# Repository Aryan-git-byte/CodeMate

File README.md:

# CodeMate - My Dev Macropad
hiii! this is my hackpad submission. built a 3x3 macropad to speed up my coding workflow

## what it does
- 9 mechanical switches in a 3x3 grid for shortcuts and macros
- rotary encoder for volume control
- 0.91" OLED that shows which key i just pressed (flashes for 1.5sec then shows "ready")
- 6 RGB LEDs that breathe in warm amber and pulse when i hit keys
- runs on Arduino (not KMK anymore) so i can use TinyUSB

## PCB
heres what the electronics look like:

| Schematic | PCB |
|-----------|-----|
|  |  |

took me a few tries to get the routing right but it works now

[x] I ran DRC and there are 0 errors but few silkscreen warnings

## Case
made in fusion360. fits everything together with M3 screws and heatset inserts

along with the top:

the switches poke through the top plate and the oled sits in a cutout. pretty clean imo

## Firmware
rewrote it in Arduino because i wanted better HID support. NO LAYERS anymore, just 9 coding shortcuts that i actually use:

**The Layout:**
```
Comment      | Format Code    | Duplicate Line
Run (F5)     | Terminal       | Close Tab
git status   | git commit     | git push
```

Encoder: Volume up/down (stays the same always)

### what each key does
- **Key 0:** Toggle comment (Ctrl+/)
- **Key 1:** Format code (Shift+Alt+F)
- **Key 2:** Duplicate line (Shift+Alt+Down)
- **Key 3:** Run code (F5)
- **Key 4:** Toggle terminal (Ctrl+`)
- **Key 5:** Close tab (Ctrl+W)
- **Key 6:** Opens terminal + runs `git status`
- **Key 7:** Opens terminal + types `git commit -m ""` with cursor inside quotes
- **Key 8:** Opens terminal + runs `git push`

git commands automatically open the VS Code terminal first (Ctrl+Shift+`) then type the command. super handy

### LED behavior
- **Normal:** slow breathing effect (10% to 40% brightness) in warm amber
- **When you press a key:** the LED near that key flashes bright then fades back to breathing
- **Color:** warm amber (255, 140, 0) because one of my LEDs has a dead blue channel lol

the oled shows which key i pressed for 1.5 seconds then goes back to showing "ready"

[x] no api keys or passwords in the code

## BOM
what you need to build this:
- 1x XIAO RP2040
- 9x Cherry MX switches  
- 9x 1N4148 diodes
- 6x SK6812 MINI-E LEDs (NOT WS2812B, different color order)
- 1x 0.91" SSD1306 OLED (128x32, I2C)
- 1x EC11 rotary encoder
- 1x 330Ω resistor (for LED data line - optional but recommended)
- 1x 1000µF capacitor (bulk cap for LEDs - optional but recommended)
- 4x M3x16mm screws
- 4x M3x5mmx4mm heatset inserts

## notes
this was fun to make! spent way too much time tweaking the firmware but learned a lot about Arduino HID and how SK6812 LEDs work differently from WS2812B.

switched from KMK to Arduino because i wanted proper keyboard+consumer HID support and the encoder was being weird in KMK. plus now i can do the breathing LED effect which looks way cooler than static colors

GG

# this is the prototype:

## and when buttons are pressed it looks like:

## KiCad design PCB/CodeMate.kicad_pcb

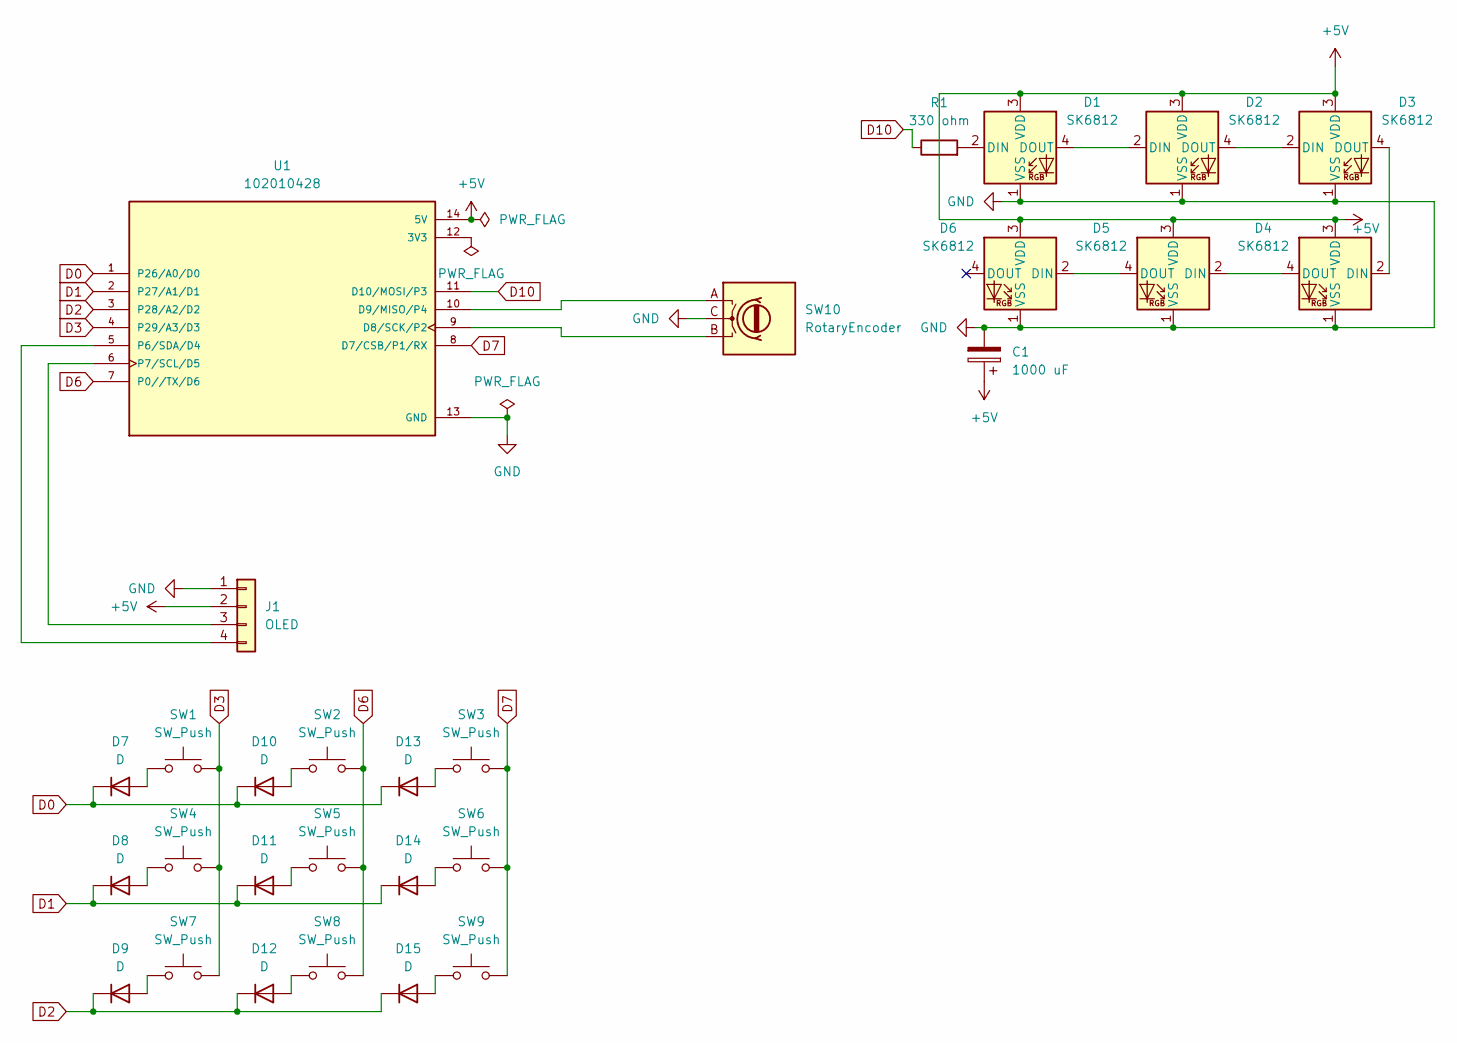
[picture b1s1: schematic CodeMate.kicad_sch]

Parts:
C1: 1000 uF; CP_Radial_D8.0mm_P3.50mm
D1, D2, D3, D4, D5, D6: SK6812; LED_SK6812MINI_PLCC4_3.5x3.5mm_P1.75mm
D7, D8, D9, D10, D11, D12, D13, D14, D15: D; D_DO-35_SOD27_P7.62mm_Horizontal
J1: OLED; PinHeader_1x04_P2.54mm_Vertical
R1: 330 ohm; R_Axial_DIN0207_L6.3mm_D2.5mm_P7.62mm_Horizontal
SW1, SW2, SW3, SW4, SW5, SW6, SW7, SW8, SW9: SW_Push; SW_Cherry_MX_1.00u_PCB
SW10: RotaryEncoder; RotaryEncoder_Alps_EC11E-Switch_Vertical_H20mm_CircularMoun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
U1: 102010428; XIAO-RP2040-DIP; PARTREV 1.3

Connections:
+5V: C1.1, D1.3 (VDD), D2.3 (VDD), D3.3 (VDD), D4.3 (VDD), D5.3 (VDD), D6.3 (VDD), J1.2, U1.14 (5V)
D0: D7.1 (K), D10.1 (K), D13.1 (K), U1.1 (P26/A0/D0)
D1: D8.1 (K), D11.1 (K), D14.1 (K), U1.2 (P27/A1/D1)
D2: D9.1 (K), D12.1 (K), D15.1 (K), U1.3 (P28/A2/D2)
D3: SW1.2, SW4.2, SW7.2, U1.4 (P29/A3/D3)
D6: SW2.2, SW5.2, SW8.2, U1.7 (P0//TX/D6)
D7: SW3.2, SW6.2, SW9.2, U1.8 (D7/CSB/P1/RX)
D10: R1.1, U1.11 (D10/MOSI/P3)
GND: C1.2, D1.1 (VSS), D2.1 (VSS), D3.1 (VSS), D4.1 (VSS), D5.1 (VSS), D6.1 (VSS), J1.1, SW10.C, U1.13 (GND)
unnamed: D1.2 (DIN), R1.2
unnamed: D1.4 (DOUT), D2.2 (DIN)
unnamed: D2.4 (DOUT), D3.2 (DIN)
unnamed: D3.4 (DOUT), D4.2 (DIN)
unnamed: D4.4 (DOUT), D5.2 (DIN)
unnamed: D5.4 (DOUT), D6.2 (DIN)
unnamed: D7.2 (A), SW1.1
unnamed: D8.2 (A), SW4.1
unnamed: D9.2 (A), SW7.1
unnamed: D10.2 (A), SW2.1
unnamed: D11.2 (A), SW5.1
unnamed: D12.2 (A), SW8.1
unnamed: D13.2 (A), SW3.1
unnamed: D14.2 (A), SW6.1
unnamed: D15.2 (A), SW9.1
unnamed: J1.3, U1.6 (P7/SCL/D5)
unnamed: J1.4, U1.5 (P6/SDA/D4)
unnamed: SW10.B, U1.9 (D8/SCK/P2)
unnamed: SW10.A, U1.10 (D9/MISO/P4)

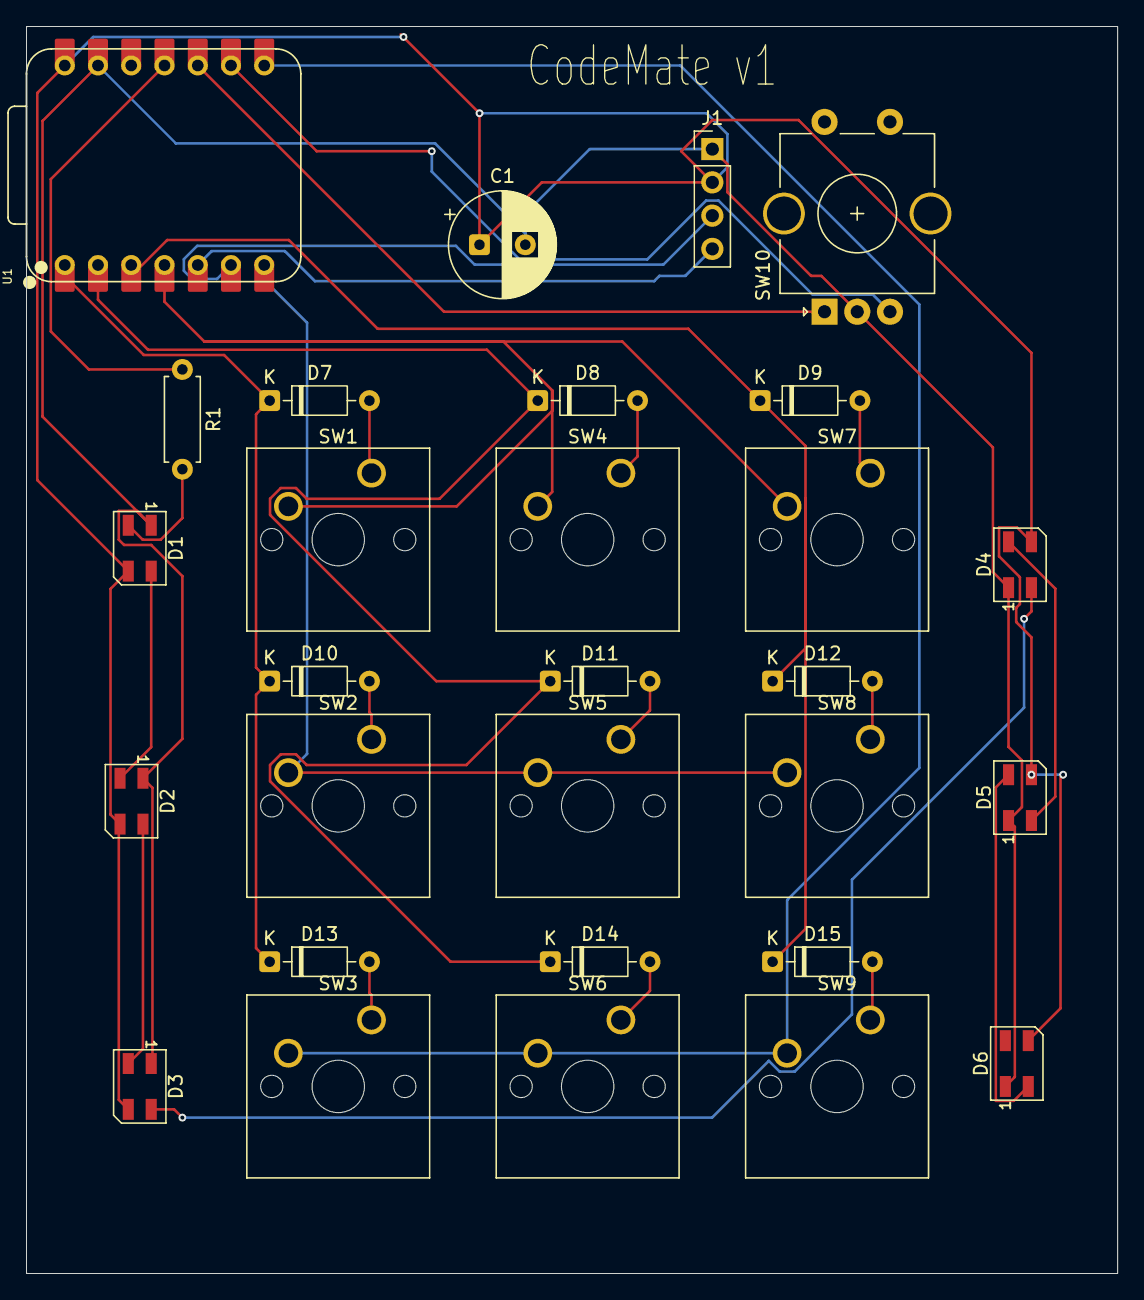
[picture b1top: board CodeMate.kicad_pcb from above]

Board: 2 copper layers, 83.3 x 95.2 mm, 29 parts (0 on the bottom side), 28 nets.

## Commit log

2026-01-25 addedd documentations
2026-01-25 updated documentations
2026-01-25 Rename CAD-body.png to cad-body.png
2026-01-29 Update README to include TODO for resource link
    Add a note to include a resource download hyperlink.
2026-01-29 Add test line Co-authored-by: FriendName <friend@email.com>
2026-01-29 Add a note of appreciation to README
2026-01-29 Create LICENSE
2026-02-20 Revise README for firmware and feature updates
    Updated the README to reflect changes in the macropad's firmware and features, including the switch from KMK to Arduino, and detailed the layout and functionality of the keys and LEDs.
2026-02-20 Revise key functions and layout in README
    Updated key functions and layout in README.md for clarity.
2026-02-20 added real image of product
